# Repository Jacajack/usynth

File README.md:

# usynth

A scalable, polyphonic 8-bit AVR synthesizer employing wavetable synthesis - a summer project that exceeded my expectations.

Features:
 - PPG Wave 2.2 wavetables
 - 2 wavetable oscillators - independent voices or a single richer one
 - 2 ASR envelope generators per voice - gain, pitch and waveform modulation
 - 1 LFO per voice - triangle or square, with fade, provides pitch and waveform modulation
 - Cluster operation to provide greater polyphony (this hasn't been tested yet, but is already implemented in the source code and _should work_&trade;)
 - 1-pole lowpass filter
 - All parameters can be adjusted as MIDI controllers
 - Presets stored in flash memory
 - MIDI pitch bend support
 - MIDI velocity sensitivity
 
MIDI controller mappings can be found [here](https://github.com/Jacajack/usynth/blob/master/midictl/usynth-midictl.ctl). If you're on Linux, you can load that file directly into [midictl](https://github.com/Jacajack/midictl) and use it to control µsynth right away.

If you want to build your own µsynth, the schematic is available in the [`hw`](https://github.com/Jacajack/usynth/tree/master/hw) directory.

See demo on YouTube:<br>

## A bit of technical background

The microcontroller is running at 20MHz (max allowed frequency at 5V). By default it's programmed to work with MCP4921 - a 12-bit SPI DAC and output samples at frequency of 28kHz. MIDI commands are received via UART0 at 31250 baud. Pins PD2, PD3 and PD4 are meant to drive status LEDs. I won't go into much detail here, because I think the source code is documented quite well.

The code is written _mostly_ in C. There are some bits in the AVR assembly language responsible for more sophisticated multiplication, but that's it. The chip is utilized pretty well with ~99% flash and ~77% RAM usage. 

The main loop is synced with timer interrupt and generates one sample per iteration. Since there are too many parameters to update all of them every sample, this work is distributed evenly accross each 21 samples. Splitting all the 'slow' code into equal pieces can be quite tricky to get right, but is definitely worth it, since it allows maximal processor time utilization.

Perhaps the most interesting bit is the synthesis process itself. The µC has waveform and wavetable data stored in flash in the same way as they were in PPG Wave (see [here](https://jacajack.github.io/music/2019/12/10/PPG-EPROM.html)). Since the AtMega328 doesn't have enough RAM to hold all the interpolated waveforms at once, everything has to be computed on the fly. In fact, I've already described this process on my blog, so I'll just refer you [there](https://jacajack.github.io/music/synths/2020/04/25/More-PPG.html).

The block diagram below represents simplified structure of a single voice. The 2 voices can be used independently or combined as a single richer one.

## Donate

If you like µsynth and want to support my future projects, you can buy me a cup of coffee below. It will be very appreciated :)

Thanks! :heart:

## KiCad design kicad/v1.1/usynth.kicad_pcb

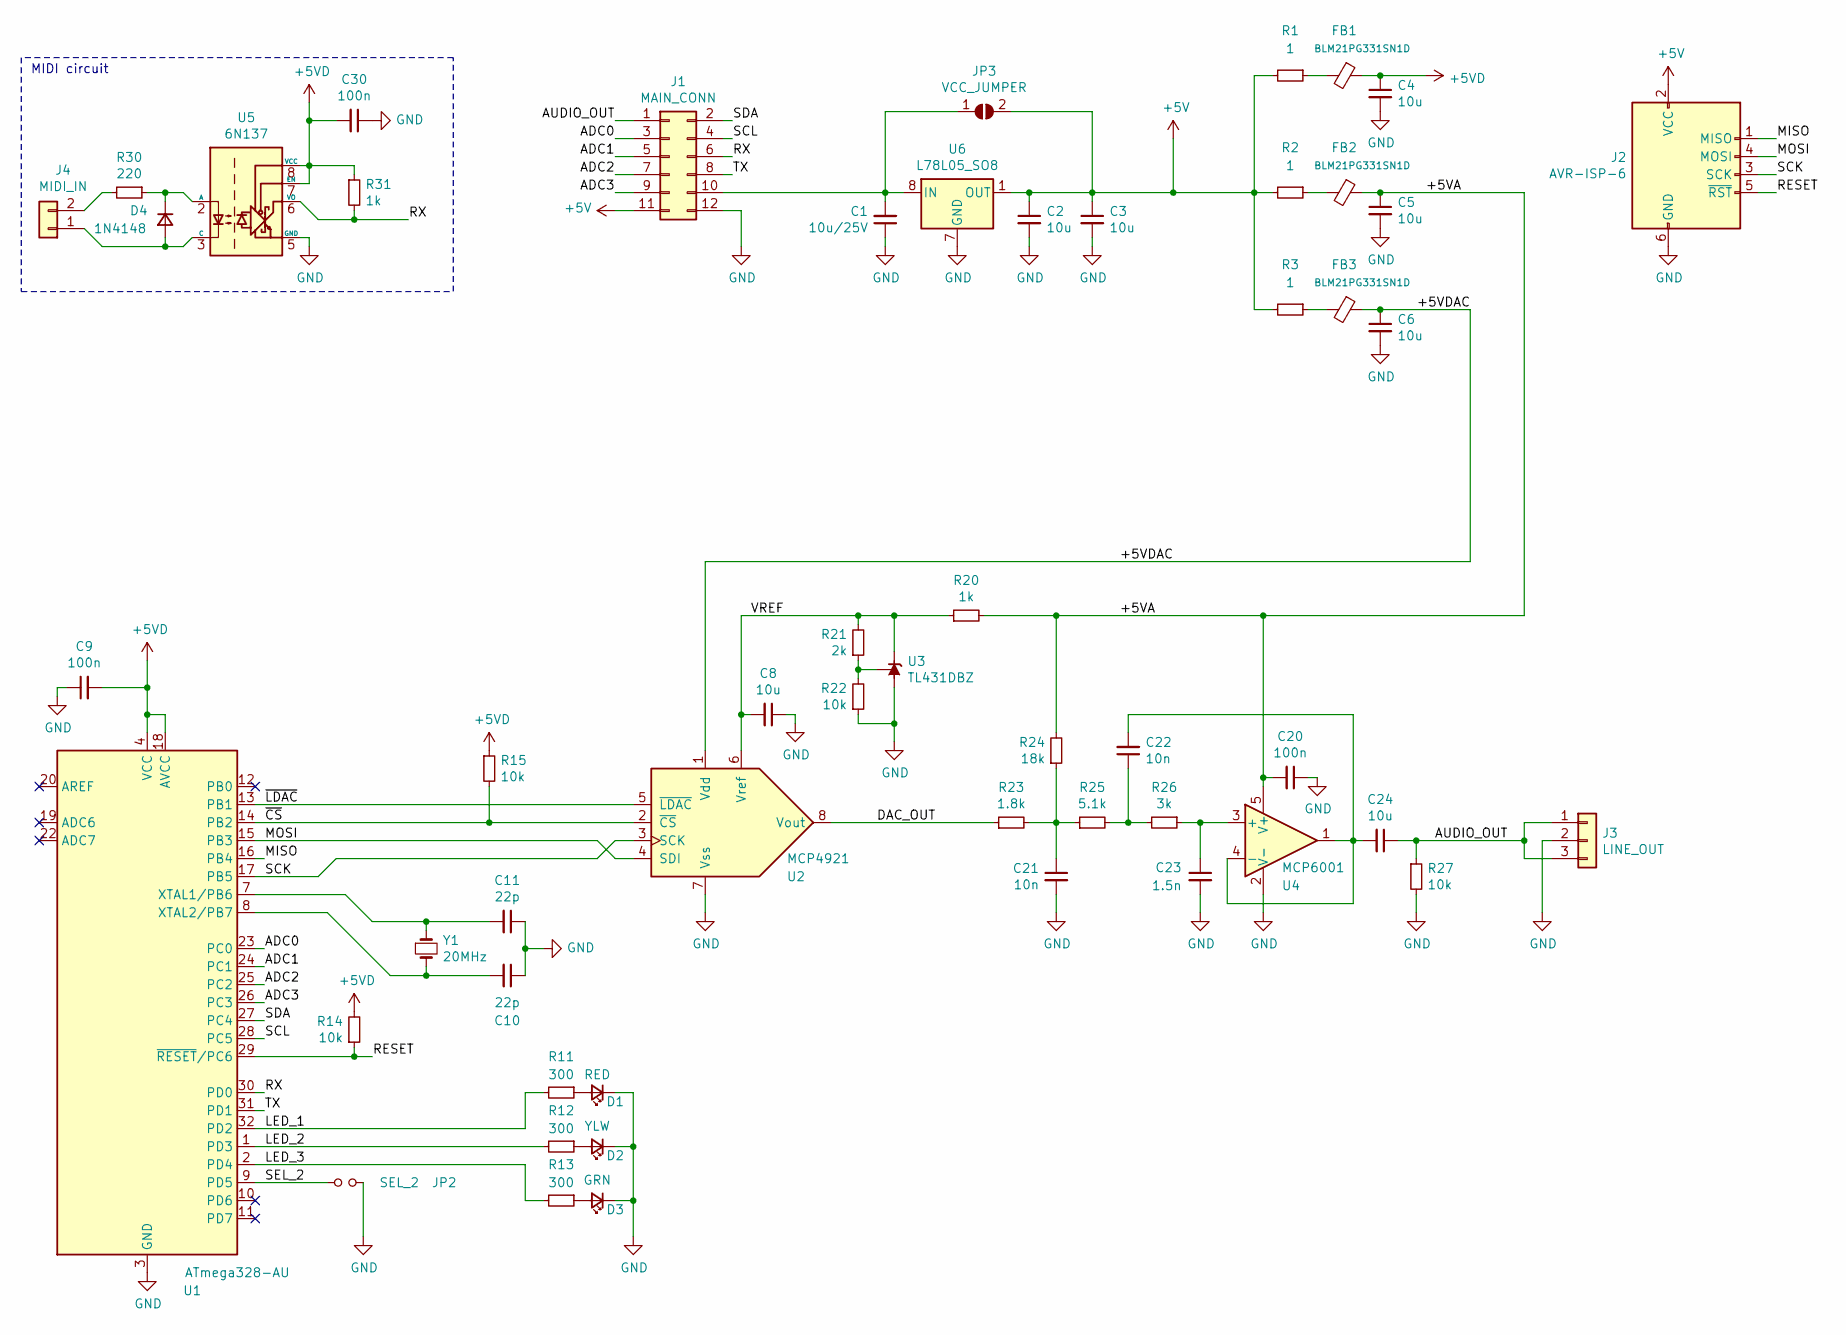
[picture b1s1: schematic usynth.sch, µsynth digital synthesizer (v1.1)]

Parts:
C1: 10u/25V; C_1206_3216Metric
C2, C3, C4, C5, C6, C8, C24: 10u; C_0805_2012Metric
C9, C20, C30: 100n; C_0805_2012Metric
C10, C11: 22p; C_0805_2012Metric
C21, C22: 10n; C_0805_2012Metric
C23: 1.5n; C_0805_2012Metric
D1: RED; LED_0805_2012Metric
D2: YLW; LED_0805_2012Metric
D3: GRN; LED_0805_2012Metric
D4: 1N4148; D_SOD-323_HandSoldering
FB1, FB2, FB3: BLM21PG331SN1D; L_0805_2012Metric
J1: MAIN_CONN; PinHeader_2x06_P2.54mm_Vertical
J2: AVR-ISP-6; PinHeader_2x03_P2.54mm_Vertical
J3: LINE_OUT; PinHeader_1x03_P2.54mm_Vertical
J4: MIDI_IN; PinHeader_1x02_P2.54mm_Vertical
JP2: SEL_2; PinHeader_1x02_P2.54mm_Vertical
JP3: VCC_JUMPER; SolderJumper-2_P1.3mm_Open_RoundedPad1.0x1.5mm
R1, R2, R3: 1; R_0805_2012Metric
R11, R12, R13: 300; R_0805_2012Metric
R14, R15, R22, R27: 10k; R_0805_2012Metric
R20, R31: 1k; R_0805_2012Metric
R21: 2k; R_0805_2012Metric
R23: 1.8k; R_0805_2012Metric
R24: 18k; R_0805_2012Metric
R25: 5.1k; R_0805_2012Metric
R26: 3k; R_0805_2012Metric
R30: 220; R_0805_2012Metric
U1: ATmega328-AU; TQFP-32_7x7mm_P0.8mm
U2: MCP4921; SOIC-8_3.9x4.9mm_P1.27mm
U3: TL431DBZ; SOT-23
U4: MCP6001; SOT-23-5
U5: 6N137; DIP-8_W7.62mm
U6: L78L05_SO8; SOIC-8_3.9x4.9mm_P1.27mm
Y1: 20MHz; Crystal_HC49-4H_Vertical

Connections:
+5V: C2.1, C3.1, J1.11, J2.2 (VCC), JP3.2 (B), R1.2, R2.2, R3.2, U6.1 (OUT)
+5VD: C4.1, C9.2, C30.2, FB1.1, R14.2, R15.1, R31.1, U1.4 (VCC), U1.6 (VCC), U1.18 (AVCC), U5.7 (EN), U5.8 (VCC)
/+5VA: C5.1, C20.2, FB2.1, R20.2, R24.2, U4.5 (V+)
/+5VDAC: C6.1, FB3.1, U2.1 (Vdd)
/ADC0: J1.3, U1.23 (PC0)
/ADC1: J1.5, U1.24 (PC1)
/ADC2: J1.7, U1.25 (PC2)
/ADC3: J1.9, U1.26 (PC3)
/AUDIO_OUT: C24.1, J1.1, J3.1, J3.3, R27.1
/DAC_OUT: R23.1, U2.8 (Vout)
/LED_1: R11.2, U1.32 (PD2)
/LED_2: R12.2, U1.1 (PD3)
/LED_3: R13.2, U1.2 (PD4)
/MISO: J2.1 (MISO), U1.16 (PB4)
/MOSI: J2.4 (MOSI), U1.15 (PB3), U2.4 (SDI)
/RESET: J2.5 (~RST), R14.1, U1.29 (~RESET~/PC6)
/RX: J1.6, R31.2, U1.30 (PD0), U5.6 (VO)
/SCK: J2.3 (SCK), U1.17 (PB5), U2.3 (SCK)
/SCL: J1.4, U1.28 (PC5)
/SDA: J1.2, U1.27 (PC4)
/SEL_2: JP2.1, U1.9 (PD5)
/TX: J1.8, U1.31 (PD1)
/VREF: C8.2, R20.1, R21.2, U2.6 (Vref), U3.1 (K)
/~CS: R15.2, U1.14 (PB2), U2.2 (~CS)
/~LDAC: U1.13 (PB1), U2.5 (~LDAC)
GND: C1.1, C2.2, C3.2, C4.2, C5.2, C6.2, C8.1, C9.1, C10.1, C11.1, C20.1, C21.2, C23.2, C30.1, D1.1 (K), D2.1 (K), D3.1 (K), J1.12, J2.6 (GND), J3.2, JP2.2, R22.1, R27.2, U1.3 (GND), U1.5 (GND), U1.21 (GND), U2.7 (Vss), U3.3 (A), U4.2 (V-), U5.5 (GND), U6.2 (GND), U6.3 (GND), U6.6 (GND), U6.7 (GND)
unnamed: C1.2, J1.10, JP3.1 (A), U6.8 (IN)
unnamed: C10.2, U1.8 (XTAL2/PB7), Y1.2
unnamed: C11.2, U1.7 (XTAL1/PB6), Y1.1
unnamed: C21.1, R23.2, R24.1, R25.1
unnamed: C22.1, R25.2, R26.2
unnamed: C22.2, C24.2, U4.1, U4.4 (-)
unnamed: C23.1, R26.1, U4.3 (+)
unnamed: D1.2 (A), R11.1
unnamed: D2.2 (A), R12.1
unnamed: D3.2 (A), R13.1
unnamed: D4.1 (K), R30.1, U5.2 (A)
unnamed: D4.2 (A), J4.1, U5.3 (C)
unnamed: FB1.2, R1.1
unnamed: FB2.2, R2.1
unnamed: FB3.2, R3.1
unnamed: J4.2, R30.2
unnamed: R21.1, R22.2, U3.2 (REF)

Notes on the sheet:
MIDI circuit

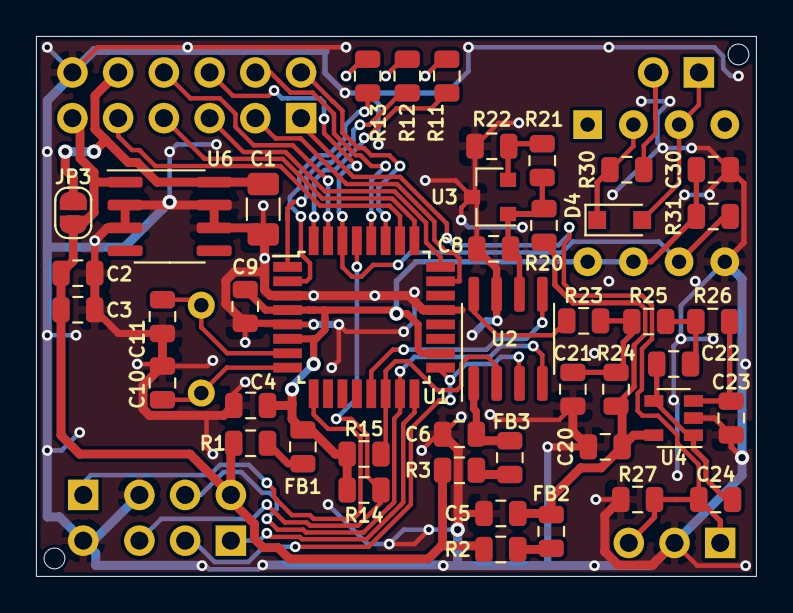
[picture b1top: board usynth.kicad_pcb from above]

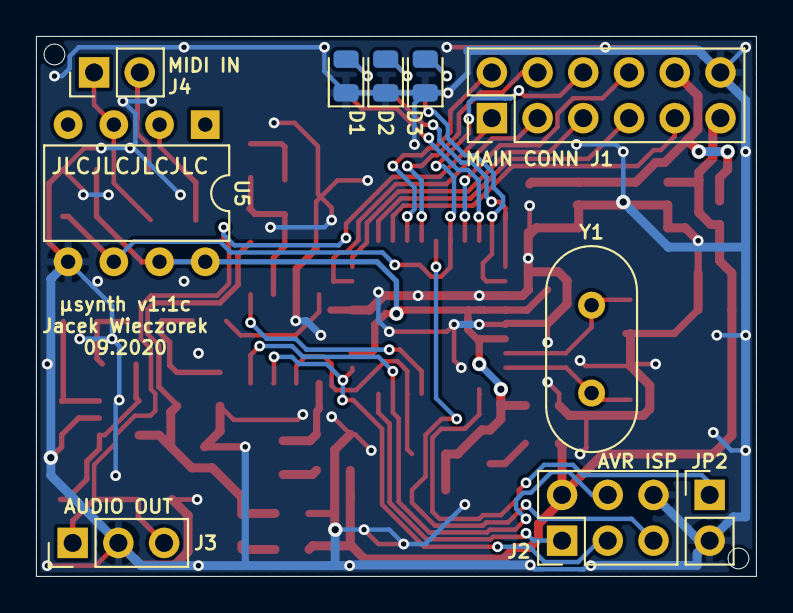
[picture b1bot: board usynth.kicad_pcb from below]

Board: 2 copper layers, 40.0 x 30.0 mm, 54 parts (10 on the bottom side), 43 nets.

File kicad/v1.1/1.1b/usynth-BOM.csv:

Comment,Designator,Footprint,LCSC
"10u, 25V, 1206",C1,Capacitor_SMD:C_1206_3216Metric,
"22p, 16V, 0805","C10,C11",Capacitor_SMD:C_0805_2012Metric,
"10n, 16V, 0805","C21,C22",Capacitor_SMD:C_0805_2012Metric,
"1.5n, 16V, 0805",C23,Capacitor_SMD:C_0805_2012Metric,
"10u, 10V, 0805","C2,C3,C4,C5,C6,C8,C24",Capacitor_SMD:C_0805_2012Metric,
"100n, 16V, 0805","C9,C20,C30",Capacitor_SMD:C_0805_2012Metric,
1N4148,D4,Diode_SMD:D_SOD-323_HandSoldering,C402214
BLM21PG331SN1D,"FB1,FB2,FB3",Inductor_SMD:L_0805_2012Metric,C74764
"300, 1%, 0805","R11,R12,R13",Resistor_SMD:R_0805_2012Metric,
"10k, 1%, 0805","R14,R15,R22,R27",Resistor_SMD:R_0805_2012Metric,
"2k, 1%, 0805",R21,Resistor_SMD:R_0805_2012Metric,
"1.8k, 1%, 0805",R23,Resistor_SMD:R_0805_2012Metric,
"18k, 1%, 0805",R24,Resistor_SMD:R_0805_2012Metric,
"5.1k, 1%, 0805",R25,Resistor_SMD:R_0805_2012Metric,
"3k, 1%, 0805",R26,Resistor_SMD:R_0805_2012Metric,
"1, 1%, 0805","R1,R2,R3",Resistor_SMD:R_0805_2012Metric,
"220, 1%, 0805",R30,Resistor_SMD:R_0805_2012Metric,
"1k, 1%, 0805","R20,R31",Resistor_SMD:R_0805_2012Metric,
ATmega328-AU,U1,Package_QFP:TQFP-32_7x7mm_P0.8mm,C14877
MCP4921,U2,Package_SO:MSOP-8_3x3mm_P0.65mm,C185506
TL431DBZ,U3,Package_TO_SOT_SMD:SOT-23,C571350
MCP601,U4,Package_TO_SOT_SMD:SOT-23-5,C128440
L78L05_SO8,U6,Package_SO:SOIC-8_3.9x4.9mm_P1.27mm,C460418

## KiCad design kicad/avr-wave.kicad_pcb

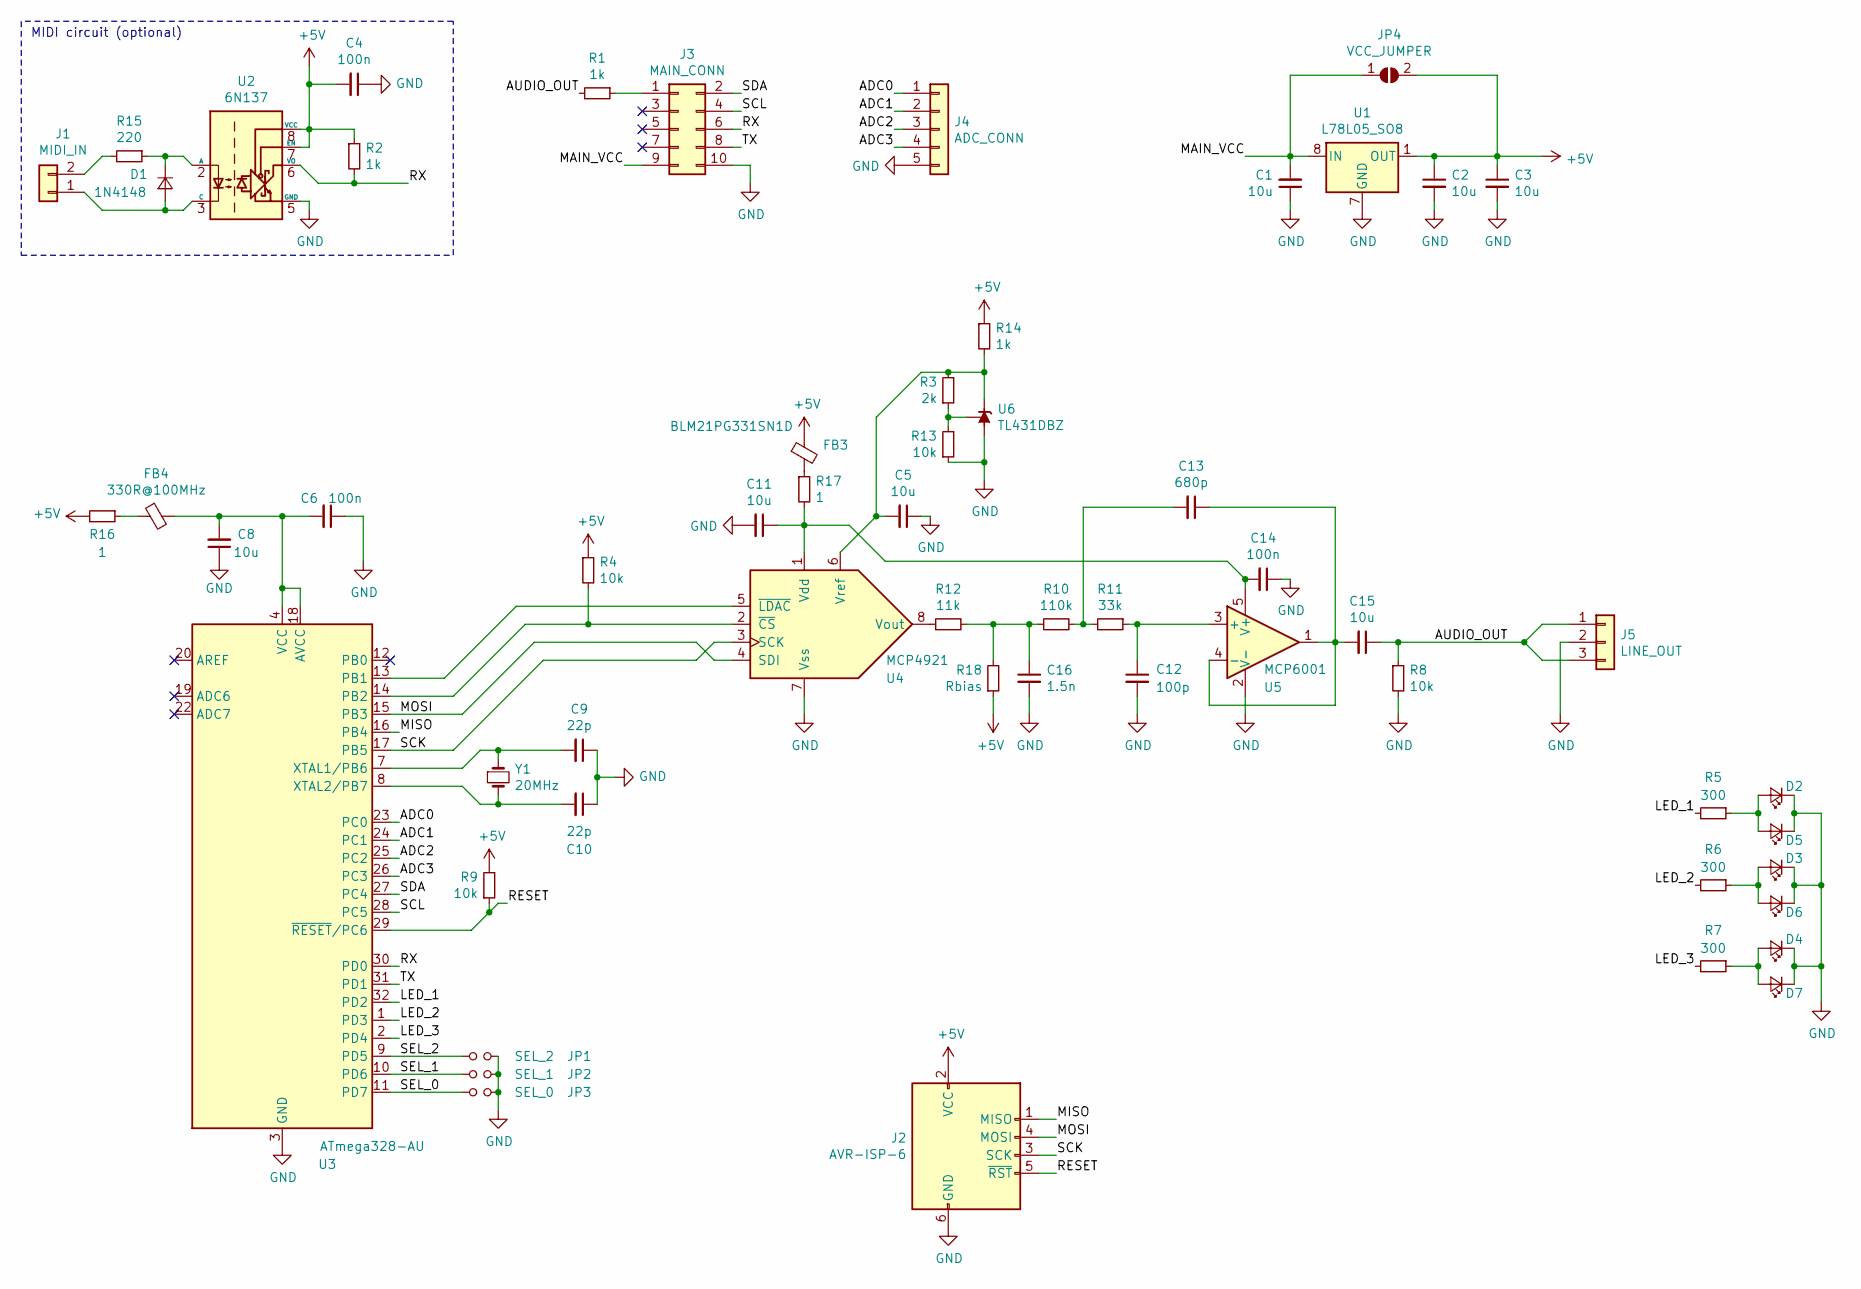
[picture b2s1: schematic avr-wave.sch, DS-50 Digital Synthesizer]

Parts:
C1, C2, C3, C5, C8, C11, C15: 10u; C_0805_2012Metric
C4, C6, C14: 100n; C_0805_2012Metric
C9, C10: 22p; C_0805_2012Metric
C12: 100p; C_0805_2012Metric
C13: 680p; C_0805_2012Metric
C16: 1.5n; C_0805_2012Metric
D1: 1N4148; D_SOD-323_HandSoldering
D2, D3, D4, D5, D6, D7: LED_Small; LED_0805_2012Metric
FB3: BLM21PG331SN1D; L_0805_2012Metric
FB4: 330R@100MHz; L_0805_2012Metric
J1: MIDI_IN; PinHeader_1x02_P2.54mm_Vertical
J2: AVR-ISP-6; PinHeader_2x03_P2.54mm_Vertical
J3: MAIN_CONN; PinSocket_2x05_P2.54mm_Vertical
J4: ADC_CONN; PinHeader_1x05_P2.54mm_Vertical
J5: LINE_OUT; PinHeader_1x03_P2.54mm_Vertical
JP1: SEL_2; PinHeader_1x02_P2.54mm_Vertical
JP2: SEL_1; PinHeader_1x02_P2.54mm_Vertical
JP3: SEL_0; PinHeader_1x02_P2.54mm_Vertical
JP4: VCC_JUMPER; SolderJumper-2_P1.3mm_Open_RoundedPad1.0x1.5mm
R1, R2, R14: 1k; R_0805_2012Metric
R3: 2k; R_0805_2012Metric
R4, R8, R9, R13: 10k; R_0805_2012Metric
R5, R6, R7: 300; R_0805_2012Metric
R10: 110k; R_0805_2012Metric
R11: 33k; R_0805_2012Metric
R12: 11k; R_0805_2012Metric
R15: 220; R_0805_2012Metric
R16, R17: 1; R_0805_2012Metric
R18: Rbias; R_0805_2012Metric
U1: L78L05_SO8; SOIC-8_3.9x4.9mm_P1.27mm
U2: 6N137; DIP-8_W7.62mm
U3: ATmega328-AU; TQFP-32_7x7mm_P0.8mm
U4: MCP4921; MSOP-8_3x3mm_P0.65mm
U5: MCP6001; SOT-23-5
U6: TL431DBZ; SOT-23
Y1: 20MHz; Crystal_HC49-4H_Vertical

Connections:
+5V: C2.1, C3.1, C4.2, FB3.1, J2.2 (VCC), JP4.2 (B), R2.1, R4.1, R9.2, R14.1, R16.2, R18.1, U1.1 (OUT), U2.7 (EN), U2.8 (VCC)
/ADC0: J4.1, U3.23 (PC0)
/ADC1: J4.2, U3.24 (PC1)
/ADC2: J4.3, U3.25 (PC2)
/ADC3: J4.4, U3.26 (PC3)
/AUDIO_OUT: C15.1, J5.1, J5.3, R1.2, R8.1
/LED_1: R5.2, U3.32 (PD2)
/LED_2: R6.2, U3.1 (PD3)
/LED_3: R7.2, U3.2 (PD4)
/MAIN_VCC: C1.2, J3.9, JP4.1 (A), U1.8 (IN)
/MISO: J2.1 (MISO), U3.16 (PB4)
/MOSI: J2.4 (MOSI), U3.15 (PB3), U4.4 (SDI)
/RESET: J2.5 (~RST), R9.1, U3.29 (~RESET~/PC6)
/RX: J3.6, R2.2, U2.6 (VO), U3.30 (PD0)
/SCK: J2.3 (SCK), U3.17 (PB5), U4.3 (SCK)
/SCL: J3.4, U3.28 (PC5)
/SDA: J3.2, U3.27 (PC4)
/SEL_0: JP3.1, U3.11 (PD7)
/SEL_1: JP2.1, U3.10 (PD6)
/SEL_2: JP1.1, U3.9 (PD5)
/TX: J3.8, U3.31 (PD1)
GND: C1.1, C2.2, C3.2, C4.1, C5.1, C6.1, C8.1, C9.1, C10.1, C11.2, C12.2, C14.1, C16.2, D2.1 (K), D3.1 (K), D4.1 (K), D5.1 (K), D6.1 (K), D7.1 (K), J2.6 (GND), J3.10, J4.5, J5.2, JP1.2, JP2.2, JP3.2, R8.2, R13.1, U1.2 (GND), U1.3 (GND), U1.6 (GND), U1.7 (GND), U2.5 (GND), U3.3 (GND), U3.5 (GND), U3.21 (GND), U4.7 (Vss), U5.2 (V-), U6.3 (A)
unnamed: C5.2, R3.2, R14.2, U4.6 (Vref), U6.1 (K)
unnamed: C6.2, C8.2, FB4.2, U3.4 (VCC), U3.6 (VCC), U3.18 (AVCC)
unnamed: C9.2, U3.7 (XTAL1/PB6), Y1.1
unnamed: C10.2, U3.8 (XTAL2/PB7), Y1.2
unnamed: C11.1, C14.2, R17.2, U4.1 (Vdd), U5.5 (V+)
unnamed: C12.1, R11.1, U5.3 (+)
unnamed: C13.1, C15.2, U5.1, U5.4 (-)
unnamed: C13.2, R10.2, R11.2
unnamed: C16.1, R10.1, R12.2, R18.2
unnamed: D1.1 (K), R15.1, U2.2 (A)
unnamed: D1.2 (A), J1.1, U2.3 (C)
unnamed: D2.2 (A), D5.2 (A), R5.1
unnamed: D3.2 (A), D6.2 (A), R6.1
unnamed: D4.2 (A), D7.2 (A), R7.1
unnamed: FB3.2, R17.1
unnamed: FB4.1, R16.1
unnamed: J1.2, R15.2
unnamed: J3.1, R1.1
unnamed: R4.2, U3.14 (PB2), U4.2 (~CS)
unnamed: R12.1, U4.8 (Vout)
unnamed: R3.1, R13.2, U6.2 (REF)
unnamed: U3.13 (PB1), U4.5 (~LDAC)

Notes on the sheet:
MIDI circuit (optional)

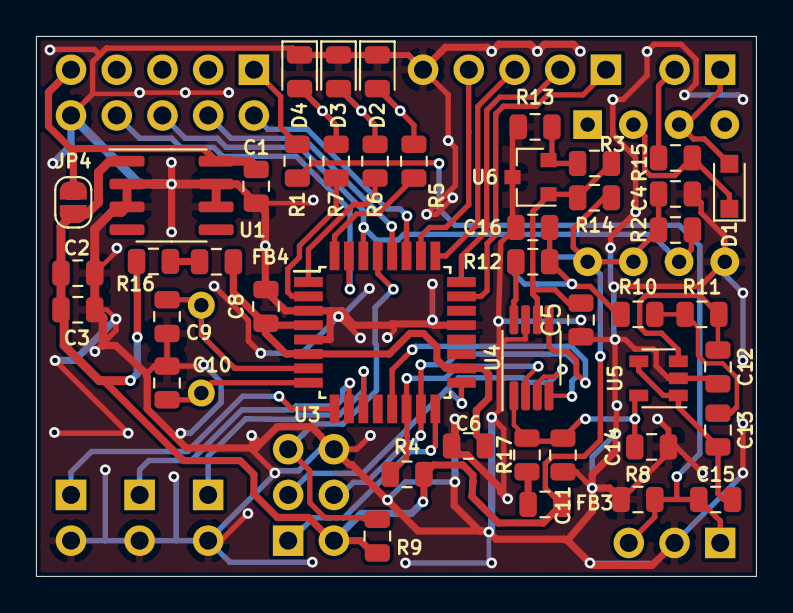
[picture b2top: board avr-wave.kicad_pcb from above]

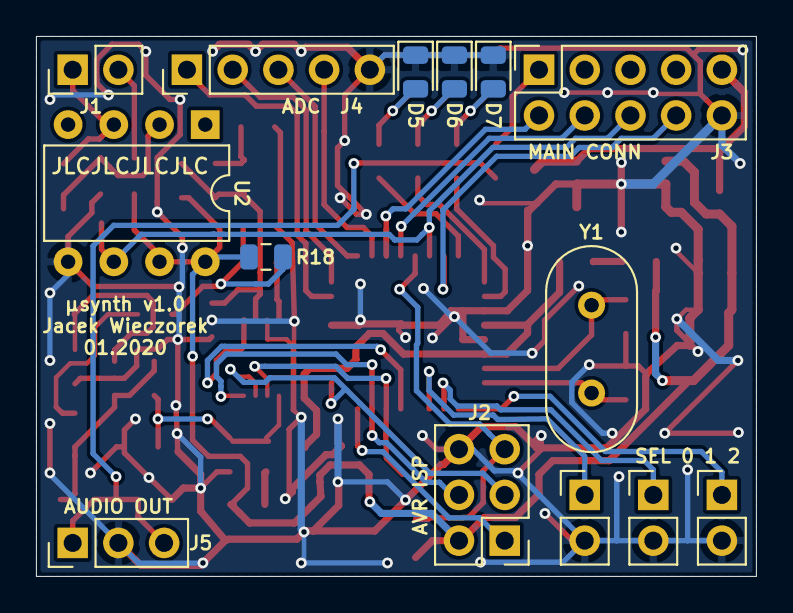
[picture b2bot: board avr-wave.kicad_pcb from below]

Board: 2 copper layers, 40.0 x 30.0 mm, 58 parts (14 on the bottom side), 44 nets.

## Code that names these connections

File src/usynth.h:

#ifndef USYNTH_H
#define USYNTH_H

#include "ppg/ppg_osc.h"
#include "eg.h"
#include "lfo.h"

// LED IO defs
#define LED_1_PIN 2
#define LED_2_PIN 3
#define LED_3_PIN 4
#define LED_RED_PIN LED_1_PIN
#define LED_YLW_PIN LED_2_PIN
#define LED_GRN_PIN LED_3_PIN

// DAC IO defs
#define LDAC_PIN  1
#define CS_PIN    2
#define MOSI_PIN  3
#define SCK_PIN   5

// DAC config bits
#define MCP4921_DAC_AB_BIT   (1 << 15)
#define MCP4921_VREF_BUF_BIT (1 << 14)
#define MCP4921_GAIN_BIT     (1 << 13)
#define MCP4921_SHDN_BIT     (1 << 12)

/**
	A single synthesizer voice
*/
typedef struct usynth_voice
{
	ppg_osc osc;
	usynth_eg amp_eg;
	usynth_eg mod_eg;
	usynth_lfo lfo;
	int8_t base_wave;
	int8_t eg_mod_int;
	int8_t lfo_mod_int;
	int8_t eg_pitch_int;
	int8_t lfo_pitch_int;
	uint8_t wavetable_number;
} usynth_voice;


#endif

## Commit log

2020-03-19 Add KiCAD files
2020-03-19 Add fp cache
2020-03-19 Improve power supply filtering
2020-03-19 Minor changes
2020-04-19 Fix Sallen-Key filter, minor PCB improvements
2020-04-27 Add gerber files
2020-04-28 Export Gebrer files again + fix silkscreen
2020-08-31 Ignore ELF files
2020-08-31 Add some test code
2020-08-31 Add wave sweep demo
2020-09-01 Add note tables and a utility to create them
2020-09-01 Add EGs and basic (and broken) polyphony
2020-09-02 Implement actualy MIDI polyphony
2020-09-02 Fix the polyphony
2020-09-02 Ignore object and deps files
2020-09-02 A proper makefile
2020-09-02 A major code cleanup
2020-09-03 Add proper MIDI controls, cleanup code and add stuff
2020-09-03 Remap attack/release controls so they make sense
2020-09-03 Update makefile (merge this commit)
2020-09-03 Properly re-trigger EGs and add a 1-pole LP filter
2020-09-03 Improve work distribution across samples
2020-09-03 Add LFO
2020-09-03 Fix a typo
2020-09-03 Implement proper MIDI programs (and two patches)
2020-09-03 Fix bug where the synthesizer would lag upon receiving any MIDI controls when the wavetable number was over 27. Make MIDI velocity affect note volume. Remove old code.
2020-09-03 Make loading wavetables much faster
2020-09-03 Improve load balancing and increase sampling frequency to 28kHz
2020-09-03 Buffer MIDI data and only process it in the load balancer to avoid audible artifacts
2020-09-04 Start working on a new PCB revision
2020-09-04 Move all generated files into one dir (and make linguist ignore them)
2020-09-04 Add usynth.lss to clean target
2020-09-04 Move notes table to data dir
2020-09-04 Move .gitattributes to the correct place
2020-09-04 All traces are connected
2020-09-04 The PCB is finished (probably)
2020-09-05 Fix issues with modulation
2020-09-05 Implement per-voice LFOs
2020-09-05 Improve load balancing
2020-09-05 Export gerber files, add PCB version suitable for JLC PCB SMT assembly
2020-09-05 Implement pitch bend and detune based on more precise MIDI note table
2020-09-05 Improve envelope table
2020-09-05 A little cleanup
2020-09-08 Split oscillator, EG and LFO banks
2020-09-08 Move MIDI presets to separate file
2020-09-08 Fix implicit declaration
2020-09-08 Remove mod_table
2020-09-08 Make env_table shorter
2020-09-09 Fix modulation value clamp
2020-09-12 Move MIDI data buffering to the main interrupt. This fixes any potential hardware buffer overruns caused by slow code in the main loop.
2020-09-17 Add working (but ugly) code for switching to mono mode. Remove config.h. Improve makefile. Fix pgm_read_delta_word(). Lesser cleanups
2020-09-18 Add MIN, MAX and CLAMP. Remove invalid +1 offset from oscillator phase step. Move usynth_voice declaration to usynth.h
2020-09-18 Add logic for operation in a cluster. Improve makefile. Minor optimizations
2020-09-18 Move part of the PPG data to EEPROM. Compile with -mrelax.
2020-09-18 Add initial draft of cluster's schematic
2020-09-18 Add Code workspace
2020-09-18 Add midictl config file and a test program
2020-09-18 Ignore map files
2020-09-18 Oscillator volume is redundant since we have sustain in EG.
2020-09-18 Increase modulation range. Split update_global() task
2020-09-18 Fix audible clicking generated by parsing MIDI messages.
    Implement fixed-size MIDI ring buffer. Move midi_process_byte to header file, so it can be inlined better. Move MIDI program loading functions to midi.c - now only program data is left in midi_progra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
2020-09-18 Go back to -O3 and add prog_fast target which neglects avrdude verification.
2020-09-18 Add new midictl config file and two test presets
2020-09-20 Slight optimization for size in the MIDI interpreter
2020-09-20 Optimize the MIDI code ever so slightly
2020-09-21 Implement pitch modulation by LFO and EG
2020-09-21 Add some more midictl files
2020-09-21 Tiny optimizations
2020-09-21 Save v0.9 binary
2020-09-21 Respond to ping requests (for cluster operation)
2020-10-22 Automatical preset compilation
2021-01-07 Add some midictl patches
2021-01-07 Add utility for converting midictl patches to header files
2021-01-07 Add some new presets
2021-01-07 Add new polyphony mode (replace newset active sound)
2021-01-29 Add temporary README and some pics
2021-01-29 Move preset files
2021-01-29 Update README, add some additional info
2021-01-29 Create LICENSE
2021-01-29 Fix YT link
2021-01-29 Update README
    Fix a typo, add a paragraph with a link to the hw directory
2021-03-04 Add FUNDING.yml
2021-08-18 Slightly optimize `safe_add_*()` functions
2021-08-18 Minimize LDAC jitter
2021-08-18 Add a new binary
2022-07-27 Add target for programming fuse bits (close #1)

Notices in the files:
README.md:
License: MIT
